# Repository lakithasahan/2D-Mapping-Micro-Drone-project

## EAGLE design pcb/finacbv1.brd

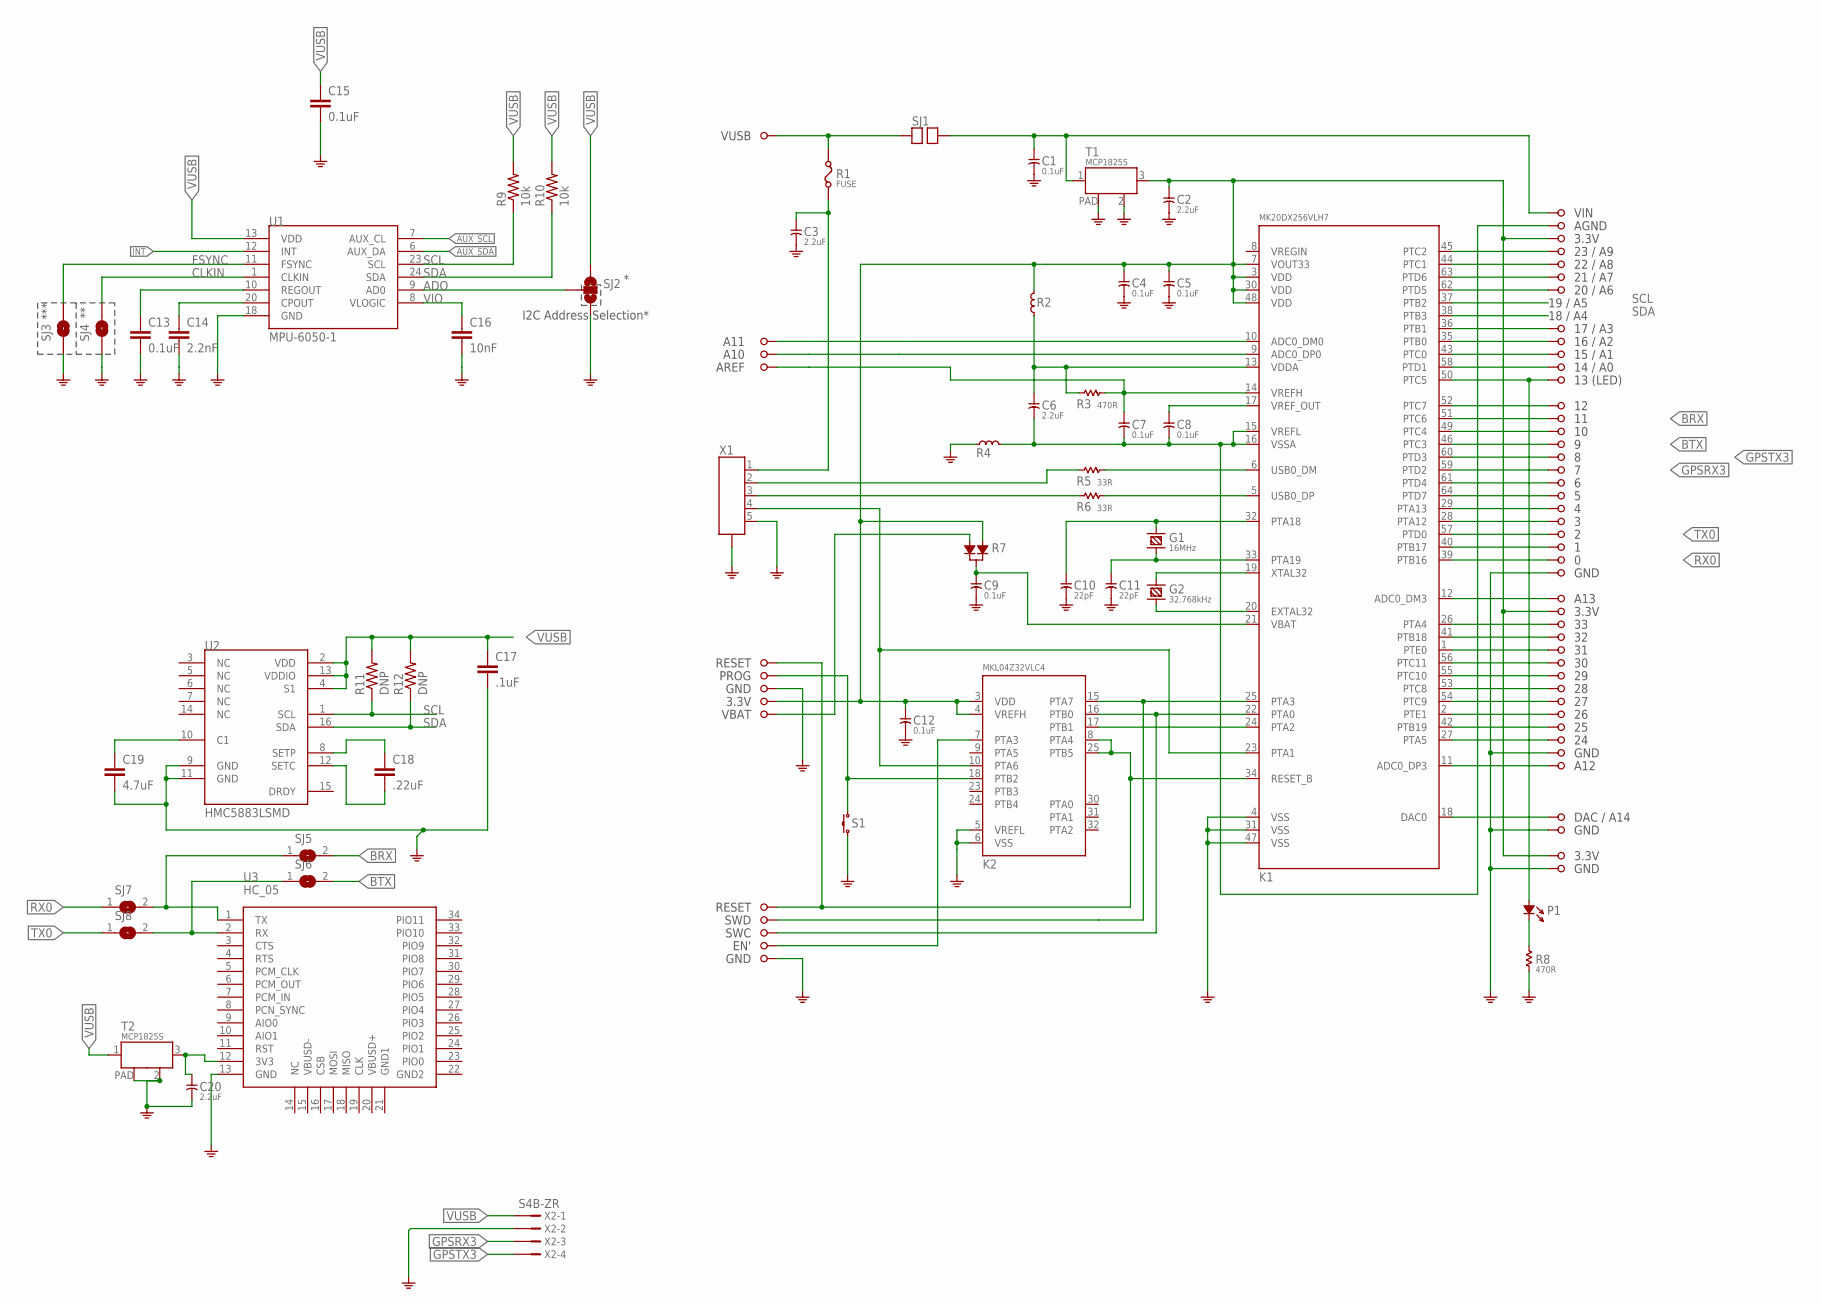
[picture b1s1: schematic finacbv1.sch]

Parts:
C1, C4, C5, C7, C8, C9, C12: 0.1uF; C0603
C2, C3, C6, C20: 2.2uF; C0805
C10, C11: 22pF; C0603
C13, C15: 0.1uF; 0603-CAP
C14: 2.2nF; 0603-CAP
C16: 10nF; 0603-CAP
C17: .1uF; 0402-CAP
C18: .22uF; 0402-CAP
C19: 4.7uF; 0402-CAP
G1: 16MHz; HC49US
G2: 32.768kHz; TC26H
K1: MK20DX256VLH7; LQFP64-05
K2: MKL04Z32VLC4; LQFP32-08
P1: LED; LED-0805
R1: FUSE; F0805
R2, R4: FERRITE; L0603
R3, R8: 470R; R0603
R5, R6: 33R; R0603
R7: DIODE_DUAL; SOT-23
R9, R10: 10k; 0603-RES
R11, R12: DNP; 0402-RES
S1: TACT_SWITCH; ALPS_SKHH
SJ1: SOLDERJUMPER
SJ2: SOLDERJUMPER_2WAYPASTE2&3; SJ_3_PASTE2&3
SJ3, SJ4: SOLDERJUMPERTRACE; SJ_2S-TRACE
SJ5, SJ6, SJ7, SJ8: SJ
SX1, SX2, SX3, SX4, SX5, SX6, SX7, SX8, SX11, SX12, SX13, SX14, SX15, SX16, SX17, SX18, SX19, SX20, SX21, SX22, SX23, SX24, SX25, SX26, SX27, SX28, SX29, SX30, SX31, SX32, SX33, SX34, SX35, SX36, SX37, SX38, SX39, SX40, SX41, SX42, SX43, SX44, SX45, SX46, SX47, SX48, SX49, SX50, SX51, SX52, SX53, SX54, SX55, SX56, SX57, SX58, SX59, SX60: PIN; PTH_39MIL
T1, T2: MCP1825S; SOT-223
U1: MPU-6050-1; QFN-24-4MM2
U2: HMC5883LSMD; 16LPCC
U3: HC_05; BLUETOOTH_SMD
X1: MINI-USB; MOLEX_SD-67503-010
X2: S4B-ZR

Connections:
ADO: SJ2.2, U1.9 (AD0)
AUX_SCL: U1.7 (AUX_CL)
AUX_SDA: U1.6 (AUX_DA)
BRX: K1.49 (PTC4), SJ5.2, SX21.1
BTX: K1.46 (PTC3), SJ6.2, SX22.1
CLKIN: SJ4.2, U1.1 (CLKIN)
FSYNC: SJ3.2, U1.11 (FSYNC)
GND: C1.2, C2.2, C3.2, C4.2, C5.2, C9.2, C10.2, C11.2, C12.2, C13.2, C14.2, C15.2, C16.2, C17.2, C19.2, C20.2, K1.4 (VSS), K1.31 (VSS), K1.47 (VSS), K2.5 (VREFL), K2.6 (VSS), R4.1, R8.1, S1.3, S1.4 (3), SJ2.3, SJ3.1, SJ4.1, SX32.1, SX42.1, SX50.1, SX53.1, SX55.1, SX60.1, T1.2 (GND), T1.PAD, T2.2 (GND), T2.PAD, U1.18 (GND), U2.9 (GND), U2.11 (GND), U3.13 (GND), X1.5, X1.P$1 (CASE), X1.P$2 (CASE), X1.P$3 (CASE), X1.P$4 (CASE), X1.P$5 (CASE), X1.P$6 (CASE), X2.2
INT: U1.12 (INT)
unnamed: K2.7 (PTA3), SX59.1
unnamed: K1.22 (PTA0), K2.16 (PTB0), SX58.1
unnamed: K1.24 (PTA2), K2.17 (PTB1)
unnamed: C14.1, U1.20 (CPOUT)
unnamed: C10.1, G1.1, K1.32 (PTA18)
unnamed: C11.1, G1.2, K1.33 (PTA19)
unnamed: G2.2 (1), K1.19 (XTAL32)
unnamed: G2.1 (2), K1.20 (EXTAL32)
unnamed: K2.18 (PTB2), S1.1, S1.2 (1), SX40.1
unnamed: K1.5 (USB0_DP), R6.2
unnamed: C8.1, K1.17 (VREF_OUT)
unnamed: K1.34 (RESET_B), K2.8 (PTA4), K2.25 (PTB5), SX38.1, SX56.1
unnamed: C7.1, K1.14 (VREFH), R3.2, SX16.1
unnamed: K1.6 (USB0_DM), R5.2
unnamed: C6.1, K1.13 (VDDA), R2.1, R3.1
unnamed: R6.1, X1.3
unnamed: R5.1, X1.2
unnamed: C3.1, R1.1, X1.1
unnamed: K1.23 (PTA1), K2.10 (PTA6), X1.4
unnamed: C13.1, U1.10 (REGOUT)
unnamed: K1.45 (PTC2), SX5.1
unnamed: K1.44 (PTC1), SX6.1
unnamed: K1.63 (PTD6), SX7.1
unnamed: K1.62 (PTD5), SX8.1
unnamed: C18.1, U2.8 (SETP)
unnamed: C18.2, U2.12 (SETC)
unnamed: K1.36 (PTB1), SX11.1
unnamed: K1.35 (PTB0), SX13.1
unnamed: K1.43 (PTC0), SX15.1
unnamed: K1.58 (PTD1), SX17.1
unnamed: K1.50 (PTC5), P1.+, SX18.1
unnamed: K1.52 (PTC7), SX19.1
unnamed: K1.51 (PTC6), SX20.1
unnamed: C20.1, T2.3 (OUT), U3.12 (3V3)
unnamed: SJ5.1, SJ7.2, U3.1 (TX)
unnamed: K1.60 (PTD3), SX23.1, X2.4
unnamed: K1.59 (PTD2), SX24.1, X2.3
unnamed: K1.61 (PTD4), SX25.1
unnamed: K1.64 (PTD7), SX26.1
unnamed: K1.29 (PTA13), SX27.1
unnamed: K1.28 (PTA12), SX28.1
unnamed: K1.57 (PTD0), SX29.1
unnamed: SJ6.1, SJ8.2, U3.2 (RX)
unnamed: K1.12 (ADC0_DM3), SX33.1
unnamed: K1.26 (PTA4), SX35.1
unnamed: K1.41 (PTB18), SX36.1
unnamed: K1.1 (PTE0), SX37.1
unnamed: K1.56 (PTC11), SX39.1
unnamed: K1.55 (PTC10), SX41.1
unnamed: K1.53 (PTC8), SX43.1
unnamed: P1.-, R8.2
unnamed: C6.2, C7.2, C8.2, K1.15 (VREFL), K1.16 (VSSA), R4.2, SX3.1
unnamed: K1.18 (DAC0), SX52.1
unnamed: K1.11 (ADC0_DP3), SX51.1
unnamed: C19.1, U2.10 (C1)
unnamed: K1.27 (PTA5), SX49.1
unnamed: K1.42 (PTB19), SX48.1
unnamed: K1.2 (PTE1), SX47.1
unnamed: K1.54 (PTC9), SX45.1
unnamed: C1.1, SJ1.2, SX2.1, T1.1 (IN)
unnamed: R7.2, SX46.1
unnamed: K1.10 (ADC0_DM0), SX12.1
unnamed: K1.9 (ADC0_DP0), SX14.1
unnamed: R1.2, SJ1.1, SX1.1
unnamed: C9.1, K1.21 (VBAT), R7.3
unnamed: C2.1, C4.1, C5.1, C12.1, K1.3 (VDD), K1.7 (VOUT33), K1.30 (VDD), K1.48 (VDD), K2.3 (VDD), K2.4 (VREFH), R2.2, R7.1, SX4.1, SX34.1, SX44.1, SX54.1, T1.3 (OUT)
unnamed: K1.25 (PTA3), K2.15 (PTA7), SX57.1
RX0: K1.39 (PTB16), SJ7.1, SX31.1
SCL: K1.37 (PTB2), R9.1, R11.1, U1.23 (SCL), U2.1 (SCL)
SDA: K1.38 (PTB3), R10.1, R12.1, U1.24 (SDA), U2.16 (SDA)
TX0: K1.40 (PTB17), SJ8.1, SX30.1
VIO: C16.1, U1.8 (VLOGIC)
VUSB: C15.1, C17.1, R9.2, R10.2, R11.2, R12.2, SJ2.1, T2.1 (IN), U1.13 (VDD), U2.2 (VDD), U2.4 (S1), U2.13 (VDDIO), X2.1

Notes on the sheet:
VIN
AGND
3.3V
23 / A9
22 / A8
21 / A7
20 / A6
19 / A5
18 / A4
17 / A3
16 / A2
15 / A1
14 / A0
13 (LED)
GND
A13
A12
DAC / A14
VBAT
RESET
PROG
A11
A10
AREF
VUSB
SWD
SWC
EN'
I2C Address Selection*
***

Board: 2 copper layers, 110 parts (0 on the bottom side), 79 nets, no tracks yet.

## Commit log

2019-02-13 flight controller pcb
